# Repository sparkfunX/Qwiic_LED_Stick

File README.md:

SparkFun Qwiic LED Stick
========================================

[*Qwiic LED Stick (SPX-14783)*](https://www.sparkfun.com/products/14783)

The Qwiic LED Stick features ten addressable APA102 LEDs, making it easy to add full color LED control using I<sup>2</sup>C. Write to individual LEDs to display a count in binary, or write to the whole strip for cool lighting effects. We’ve written an Arduino library that takes care of the I<sup>2</sup>C and communication to the LEDs so all you have to do is decide what color each LED should be.

This board is one of our many [Qwiic](https://www.sparkfun.com/qwiic) compatible boards! Simply plug and go. No soldering, no figuring out which is SDA or SCL, and no voltage regulation or translation required!

SparkFun labored with love to create this code. Feel like supporting open source hardware? 
Buy a [board](https://www.sparkfun.com/products/14783) from SparkFun!

Repository Contents
-------------------

* **/Firmware** - Firmware
* **/Hardware** - Eagle design files (.brd, .sch)

Library
--------------
* **[Arduino Library](https://github.com/sparkfun/SparkFun_Qwiic_LED_Stick_Arduino_Library)** - Library for Qwiic LED Stick

License Information
-------------------

This product is _**open source**_! 

If you have any questions or concerns on licensing, please contact techsupport@sparkfun.com.

Please use, reuse, and modify these files as you see fit. Please maintain attribution to SparkFun Electronics and release any derivative under the same license.

Distributed as-is; no warranty is given.

- Your friends at SparkFun.

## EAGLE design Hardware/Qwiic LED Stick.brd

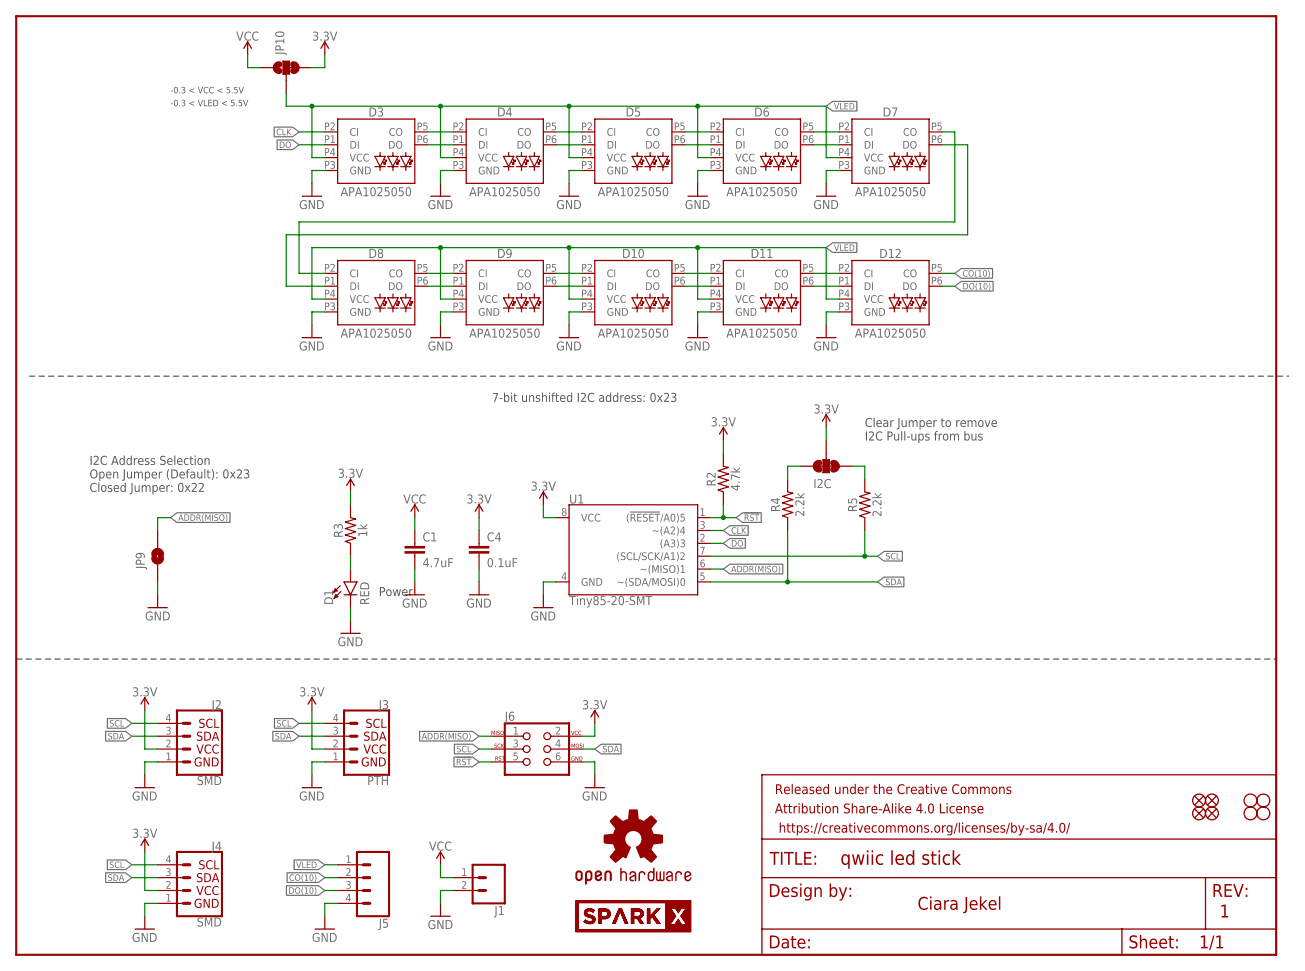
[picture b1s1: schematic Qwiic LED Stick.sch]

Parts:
C1: 4.7uF; 0603
C4: 0.1uF; 0603
D1: RED; LED-0603
D3, D4, D5, D6, D7, D8, D9, D10, D11, D12: APA1025050; APA102-5050
FRAME1: FRAME-LETTER; CREATIVE_COMMONS
I2C: JUMPER-SMT_3_2-NC_TRACE_SILK; SMT-JUMPER_3_2-NC_TRACE_SILK
J1: CONN_021X02_NO_SILK; 1X02_NO_SILK
J2, J4: SMD; 1X04_1MM_RA
J3: PTH; 1X04_NO_SILK
J5: CONN_041X04_NO_SILK; 1X04_NO_SILK
J6: AVR_SPI_PROG_3X2TESTPOINTS; 2X3_TEST_POINTS
JP1, JP2, JP5, JP6: FIDUCIALUFIDUCIAL; MICRO-FIDUCIAL
JP3, JP4, JP7, JP8: STAND-OFF
JP9: JUMPER-SMT_2_NO_SILK; SMT-JUMPER_2_NO_SILK
JP10: JUMPER-SMT_3_1-NC_TRACE_SILK; SMT-JUMPER_3_1-NC_TRACE_SILK
LOGO1: OSHW-LOGOMINI; OSHW-LOGO-MINI
R2: 4.7k; 0603
R3: 1k; 0603
R4, R5: 2.2k; 0603
U1: Tiny85-20-SMT; SO08-EIAJ_MCU
U$1, U$2: SPARKX-LOGO4; SPARKX-MEDIUM

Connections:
3.3V: C4.1, I2C.2, J2.2 (VCC), J3.2 (VCC), J4.2 (VCC), J6.2, JP10.3, R2.2, R3.2, U1.8 (VCC)
!RST: J6.5, R2.1, U1.1 ((!RESET!/A0)5)
ADDR(MISO): J6.1, JP9.2, U1.6 (~(MISO)1)
CLK: D3.P2 (CI), U1.3 (~(A2)4)
CO(10): D12.P5 (CO), J5.2
DO: D3.P1 (DI), U1.2 ((A3)3)
DO(10): D12.P6 (DO), J5.3
GND: C1.2, C4.2, D1.C, D3.P3 (GND), D4.P3 (GND), D5.P3 (GND), D6.P3 (GND), D7.P3 (GND), D8.P3 (GND), D9.P3 (GND), D10.P3 (GND), D11.P3 (GND), D12.P3 (GND), J1.2, J2.1 (GND), J3.1 (GND), J4.1 (GND), J5.4, J6.6, JP9.1, U1.4 (GND)
unnamed: I2C.1, R5.2
unnamed: I2C.3, R4.2
unnamed: D1.A, R3.1
unnamed: D11.P6 (DO), D12.P1 (DI)
unnamed: D11.P5 (CO), D12.P2 (CI)
unnamed: D10.P5 (CO), D11.P2 (CI)
unnamed: D10.P6 (DO), D11.P1 (DI)
unnamed: D9.P5 (CO), D10.P2 (CI)
unnamed: D9.P6 (DO), D10.P1 (DI)
unnamed: D8.P5 (CO), D9.P2 (CI)
unnamed: D8.P6 (DO), D9.P1 (DI)
unnamed: D7.P5 (CO), D8.P2 (CI)
unnamed: D7.P6 (DO), D8.P1 (DI)
unnamed: D6.P5 (CO), D7.P2 (CI)
unnamed: D6.P6 (DO), D7.P1 (DI)
unnamed: D5.P6 (DO), D6.P1 (DI)
unnamed: D5.P5 (CO), D6.P2 (CI)
unnamed: D4.P6 (DO), D5.P1 (DI)
unnamed: D4.P5 (CO), D5.P2 (CI)
unnamed: D3.P5 (CO), D4.P2 (CI)
unnamed: D3.P6 (DO), D4.P1 (DI)
SCL: J2.4 (SCL), J3.4 (SCL), J4.4 (SCL), J6.3, R5.1, U1.7 ((SCL/SCK/A1)2)
SDA: J2.3 (SDA), J3.3 (SDA), J4.3 (SDA), J6.4, R4.1, U1.5 (~(SDA/MOSI)0)
VCC: C1.1, J1.1, JP10.1
VLED: D3.P4 (VCC), D4.P4 (VCC), D5.P4 (VCC), D6.P4 (VCC), D7.P4 (VCC), D8.P4 (VCC), D9.P4 (VCC), D10.P4 (VCC), D11.P4 (VCC), D12.P4 (VCC), J5.1, JP10.2

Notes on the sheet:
Clear Jumper to remove I2C Pull-ups from bus
Power
Ciara Jekel
7-bit unshifted I2C address: 0x23
I2C Address Selection Open Jumper (Default): 0x23 Closed Jumper: 0x22
-0.3 < VCC < 5.5V
-0.3 < VLED < 5.5V

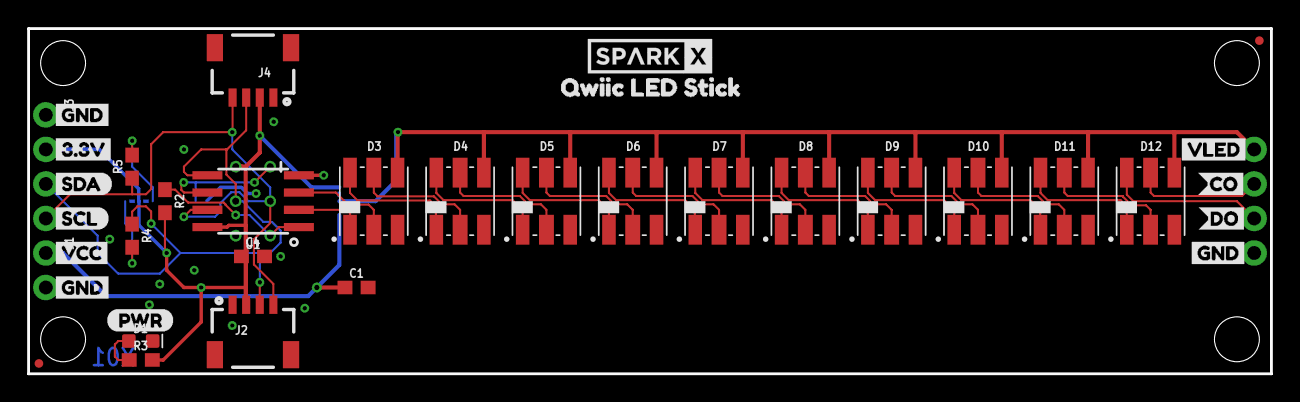
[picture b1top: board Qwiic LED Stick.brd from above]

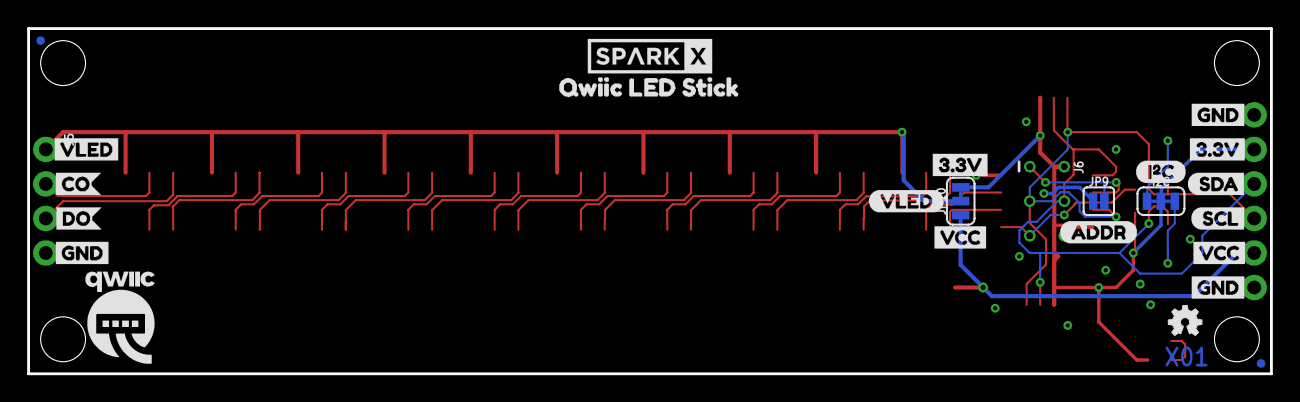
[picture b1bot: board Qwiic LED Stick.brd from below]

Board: 2 copper layers, 91.4 x 25.4 mm, 68 parts (26 on the bottom side), 33 nets.

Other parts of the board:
U$3, U$8, U$12, U$22: GND1
U$4, U$21: 3#3V2
U$5, U$9: VLED4
U$6: DO8
U$7: CO5
U$10: (PWR)
U$11: (I_SUPER2_C)
U$13, U$32: QWIIC_LED_STICK1
U$15: DO12
U$16: CO9
U$17: SDA0
U$18: SCL1
U$19, U$20, U$31: VCC1
U$23, U$24: GND0
U$25: VLED3
U$26: SCL9
U$27: SDA8
U$28: ADDR2
U$29: QWIIC-LOGO-MEDIUM
U$30: 3#3V3

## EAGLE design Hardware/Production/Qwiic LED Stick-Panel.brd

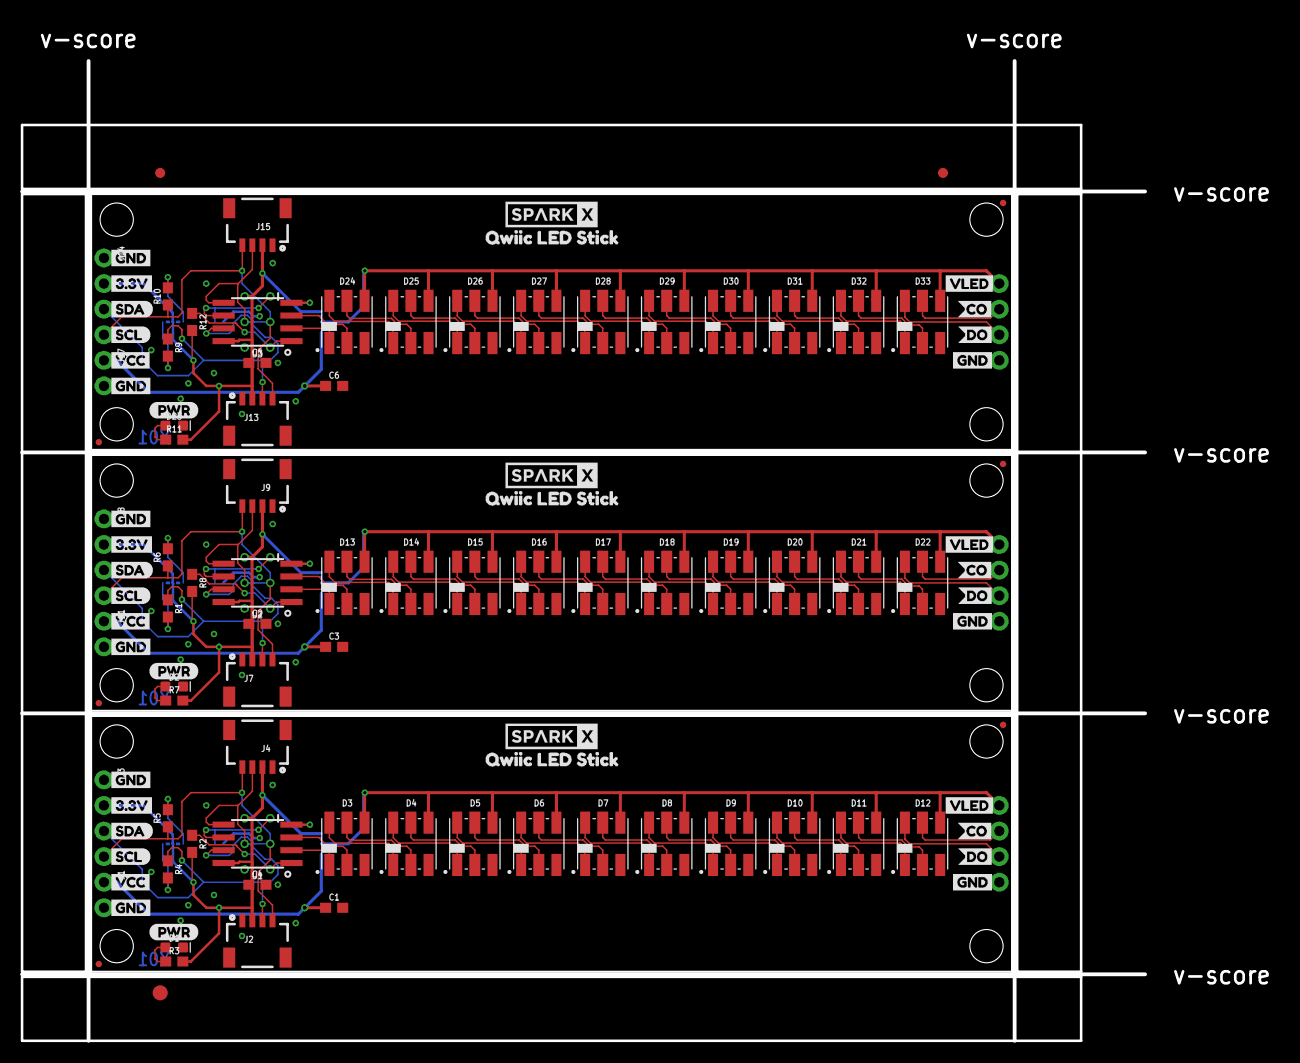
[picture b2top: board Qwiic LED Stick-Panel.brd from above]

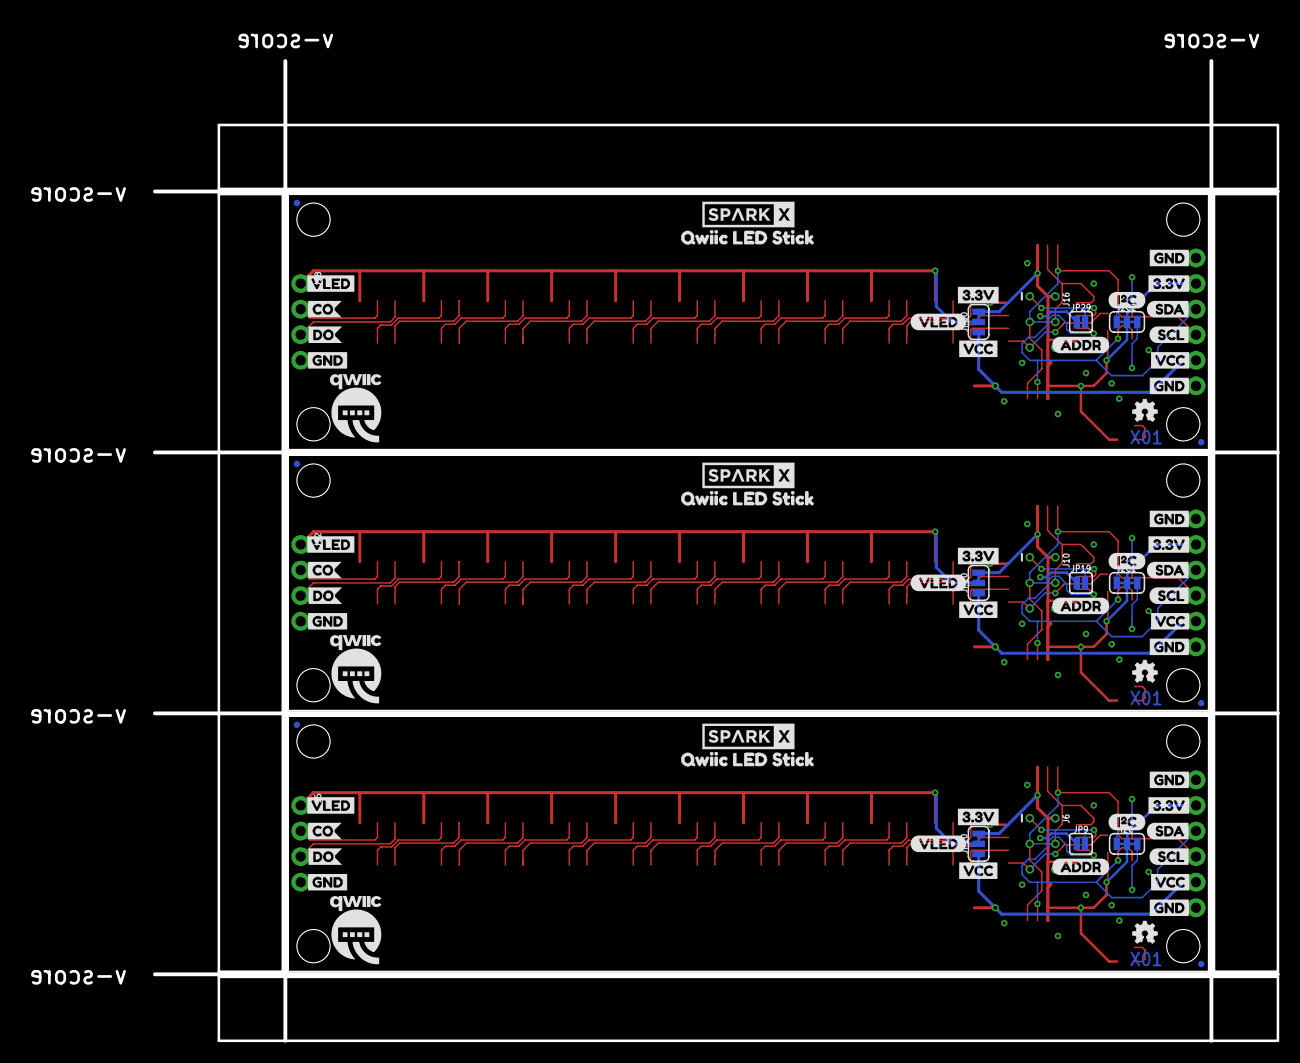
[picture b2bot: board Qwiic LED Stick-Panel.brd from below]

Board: 2 copper layers, 111.5 x 97.3 mm, 204 parts (78 on the bottom side), 99 nets.

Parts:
C1, C3, C6: 4.7uF; 0603
C2, C4, C5: 0.1uF; 0603
D1, D2, D23: RED; LED-0603
D3, D4, D5, D6, D7, D8, D9, D10, D11, D12, D13, D14, D15, D16, D17, D18, D19, D20, D21, D22, D24, D25, D26, D27, D28, D29, D30, D31, D32, D33: APA1025050; APA102-5050
E$1, E$2: FIDUCIAL-1X2
E$3: FIDUCIAL-1.5X3
I2C, I2C1, I2C2: SMT-JUMPER_3_2-NC_TRACE_SILK
J1, J11, J17: 1X02_NO_SILK
J2, J4, J7, J9, J13, J15: SMD; 1X04_1MM_RA
J3, J8, J14: PTH; 1X04_NO_SILK
J5, J12, J18: 1X04_NO_SILK
J6, J10, J16: AVR_SPI_PROG_3X2TESTPOINTS; 2X3_TEST_POINTS
JP1, JP2, JP5, JP6, JP13, JP14, JP15, JP16, JP23, JP24, JP25, JP26: FIDUCIALUFIDUCIAL; MICRO-FIDUCIAL
JP3, JP4, JP7, JP8, JP11, JP12, JP17, JP18, JP21, JP22, JP27, JP28: STAND-OFF
JP9, JP19, JP29: JUMPER-SMT_2_NO_SILK; SMT-JUMPER_2_NO_SILK
JP10, JP20, JP30: SMT-JUMPER_3_1-NC_TRACE_SILK
LOGO1, LOGO2, LOGO3: OSHW-LOGOMINI; OSHW-LOGO-MINI
R1, R4, R5, R6, R9, R10: 2.2k; 0603
R2, R8, R12: 4.7k; 0603
R3, R7, R11: 1k; 0603
U1, U2, U3: Tiny85-20-SMT; SO08-EIAJ_MCU
U$1, U$2, U$14, U$33, U$63, U$64: SPARKX-LOGO4; SPARKX-MEDIUM
U$3, U$8, U$12, U$22, U$35, U$38, U$44, U$52, U$66, U$69, U$75, U$83: GND1
U$4, U$21, U$34, U$39, U$65, U$70: 3#3V2
U$5, U$9, U$43, U$49, U$74, U$80: VLED4
U$6, U$50, U$81: DO8
U$7, U$51, U$82: CO5
U$10, U$40, U$71: (PWR)
U$11, U$41, U$72: (I_SUPER2_C)
U$13, U$32, U$61, U$62, U$92, U$93: QWIIC_LED_STICK1
U$15, U$45, U$76: DO12
U$16, U$46, U$77: CO9
U$17, U$47, U$78: SDA0
U$18, U$48, U$79: SCL1
U$19, U$20, U$31, U$53, U$54, U$60, U$84, U$85, U$91: VCC1
U$23, U$24, U$55, U$56, U$86, U$87: GND0
U$25, U$57, U$88: VLED3
U$26, U$36, U$67: SCL9
U$27, U$37, U$68: SDA8
U$28, U$58, U$89: ADDR2
U$29, U$42, U$73: QWIIC-LOGO-MEDIUM
U$30, U$59, U$90: 3#3V3

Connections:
3.3V: C4.1, I2C.2, J2.2, J3.2, J4.2, J6.2, JP10.3, R2.2, R3.2, U1.8
3.3V1: C2.1, I2C1.2, J7.2, J8.2, J9.2, J10.2, JP20.3, R7.2, R8.2, U2.8
3.3V2: C5.1, I2C2.2, J13.2, J14.2, J15.2, J16.2, JP30.3, R11.2, R12.2, U3.8
!RST: J6.5, R2.1, U1.1
!RST1: J10.5, R8.1, U2.1
!RST2: J16.5, R12.1, U3.1
ADDR(MISO): J6.1, JP9.2, U1.6
ADDR(MISO)1: J10.1, JP19.2, U2.6
ADDR(MISO)2: J16.1, JP29.2, U3.6
CLK: D3.P2, U1.3
CLK1: D13.P2, U2.3
CLK2: D24.P2, U3.3
CO(10): D12.P5, J5.2
CO(10)1: D22.P5, J12.2
CO(10)2: D33.P5, J18.2
DO: D3.P1, U1.2
DO1: D13.P1, U2.2
DO2: D24.P1, U3.2
DO(10): D12.P6, J5.3
DO(10)1: D22.P6, J12.3
DO(10)2: D33.P6, J18.3
GND: C1.2, C4.2, D1.C, D3.P3, D4.P3, D5.P3, D6.P3, D7.P3, D8.P3, D9.P3, D10.P3, D11.P3, D12.P3, J1.2, J2.1, J3.1, J4.1, J5.4, J6.6, JP9.1, U1.4
GND1: C2.2, C3.2, D2.C, D13.P3, D14.P3, D15.P3, D16.P3, D17.P3, D18.P3, D19.P3, D20.P3, D21.P3, D22.P3, J7.1, J8.1, J9.1, J10.6, J11.2, J12.4, JP19.1, U2.4
GND2: C5.2, C6.2, D23.C, D24.P3, D25.P3, D26.P3, D27.P3, D28.P3, D29.P3, D30.P3, D31.P3, D32.P3, D33.P3, J13.1, J14.1, J15.1, J16.6, J17.2, J18.4, JP29.1, U3.4
unnamed: I2C.1, R5.2
unnamed: I2C.3, R4.2
unnamed: D1.A, R3.1
unnamed: I2C1.1, R6.2
unnamed: I2C1.3, R1.2
unnamed: D2.A, R7.1
unnamed: D21.P6, D22.P1
unnamed: D11.P6, D12.P1
unnamed: D11.P5, D12.P2
unnamed: D10.P5, D11.P2
unnamed: D10.P6, D11.P1
unnamed: D9.P5, D10.P2
unnamed: D9.P6, D10.P1
unnamed: D8.P5, D9.P2
unnamed: D8.P6, D9.P1
unnamed: D7.P5, D8.P2
unnamed: D7.P6, D8.P1
unnamed: D6.P5, D7.P2
unnamed: D6.P6, D7.P1
unnamed: D5.P6, D6.P1
unnamed: D5.P5, D6.P2
unnamed: D4.P6, D5.P1
unnamed: D4.P5, D5.P2
unnamed: D3.P5, D4.P2
unnamed: D3.P6, D4.P1
unnamed: D21.P5, D22.P2
unnamed: D20.P5, D21.P2
unnamed: D20.P6, D21.P1
unnamed: D19.P5, D20.P2
unnamed: D19.P6, D20.P1
unnamed: D18.P5, D19.P2
unnamed: D18.P6, D19.P1
unnamed: D17.P5, D18.P2
unnamed: D17.P6, D18.P1
unnamed: D16.P5, D17.P2
unnamed: D16.P6, D17.P1
unnamed: D15.P6, D16.P1
unnamed: D15.P5, D16.P2
unnamed: D14.P6, D15.P1
unnamed: D14.P5, D15.P2
unnamed: D13.P5, D14.P2
unnamed: D13.P6, D14.P1
unnamed: I2C2.1, R10.2
unnamed: I2C2.3, R9.2
unnamed: D23.A, R11.1
unnamed: D32.P6, D33.P1
unnamed: D32.P5, D33.P2
unnamed: D31.P5, D32.P2
unnamed: D31.P6, D32.P1
unnamed: D30.P5, D31.P2
unnamed: D30.P6, D31.P1
unnamed: D29.P5, D30.P2
unnamed: D29.P6, D30.P1
unnamed: D28.P5, D29.P2
unnamed: D28.P6, D29.P1
unnamed: D27.P5, D28.P2
unnamed: D27.P6, D28.P1
unnamed: D26.P6, D27.P1
unnamed: D26.P5, D27.P2
unnamed: D25.P6, D26.P1
unnamed: D25.P5, D26.P2
unnamed: D24.P5, D25.P2
unnamed: D24.P6, D25.P1
SCL: J2.4, J3.4, J4.4, J6.3, R5.1, U1.7
SCL1: J7.4, J8.4, J9.4, J10.3, R6.1, U2.7
SCL2: J13.4, J14.4, J15.4, J16.3, R10.1, U3.7
SDA: J2.3, J3.3, J4.3, J6.4, R4.1, U1.5
SDA1: J7.3, J8.3, J9.3, J10.4, R1.1, U2.5
SDA2: J13.3, J14.3, J15.3, J16.4, R9.1, U3.5
VCC: C1.1, J1.1, JP10.1
VCC1: C3.1, J11.1, JP20.1
VCC2: C6.1, J17.1, JP30.1
VLED: D3.P4, D4.P4, D5.P4, D6.P4, D7.P4, D8.P4, D9.P4, D10.P4, D11.P4, D12.P4, J5.1, JP10.2
VLED1: D13.P4, D14.P4, D15.P4, D16.P4, D17.P4, D18.P4, D19.P4, D20.P4, D21.P4, D22.P4, J12.1, JP20.2
VLED2: D24.P4, D25.P4, D26.P4, D27.P4, D28.P4, D29.P4, D30.P4, D31.P4, D32.P4, D33.P4, J18.1, JP30.2

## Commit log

2018-05-25 inital
2018-05-25 Hardware added
2018-05-25 name updates
    for consistency
2018-05-29 added examples
2018-05-30 firmware and example updates
    fixed sleep mode in firmware
2018-05-31 bug fixes
2018-05-31 brightness example
2018-05-31 cleanup
2018-06-08 examples and library
2018-06-08 library fixes
2018-06-11 update schematic
2018-06-11 firmware aesthetic update
2018-06-11 length update
2018-06-12 git ignore
2018-06-12 added README
2018-06-12 fix README
2018-06-13 added dimensions
2020-05-07 Add programming script

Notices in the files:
parts and their libraries:
SparkFun-Resistors: Licensing: Creative Commons ShareAlike 4.0 International - https://creativecommons.org/licenses/by-sa/4.0
SparkFun-Aesthetics: Released under the Creative Commons Attribution Share-Alike 4.0 License
SparkFun-Aesthetics: https://creativecommons.org/licenses/by-sa/4.0
